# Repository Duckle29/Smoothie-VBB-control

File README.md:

# Smoothie-VBB-control
A small board, meant to switch the VBB rail on a smoothieboard, to allow the board to cut the power to stepper motors and heaters

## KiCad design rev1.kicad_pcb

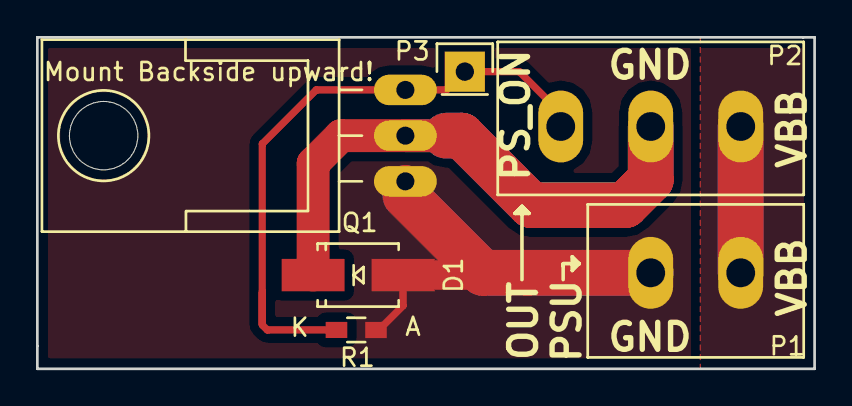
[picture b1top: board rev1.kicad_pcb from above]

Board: 2 copper layers, 43.2 x 18.4 mm, 6 parts (0 on the bottom side), 4 nets.

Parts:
D1: 1N4007; SMA_Handsoldering
P1: CONN_01X02; FCI_20020107-2p
P2: CONN_01X03; FCI_20020107-3p
P3: CONN_01X01; Pin_Header_Straight_1x01
Q1: AOT240L; TO-220_Neutral123_Horizontal_Reverse_LargePads
R1: 10k; R_0603_HandSoldering

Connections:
GND: D1.2, P1.1, Q1.3, R1.1
unnamed: D1.1, P2.2, Q1.2
unnamed: P1.2, P2.1
unnamed: P2.3, P3.1, Q1.1, R1.2

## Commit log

2016-06-23 Added PDF of schematic, and renders of board
